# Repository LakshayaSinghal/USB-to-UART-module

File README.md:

# USB-to-UART-module
Small sized PCB for a USB to UART module using CP2102

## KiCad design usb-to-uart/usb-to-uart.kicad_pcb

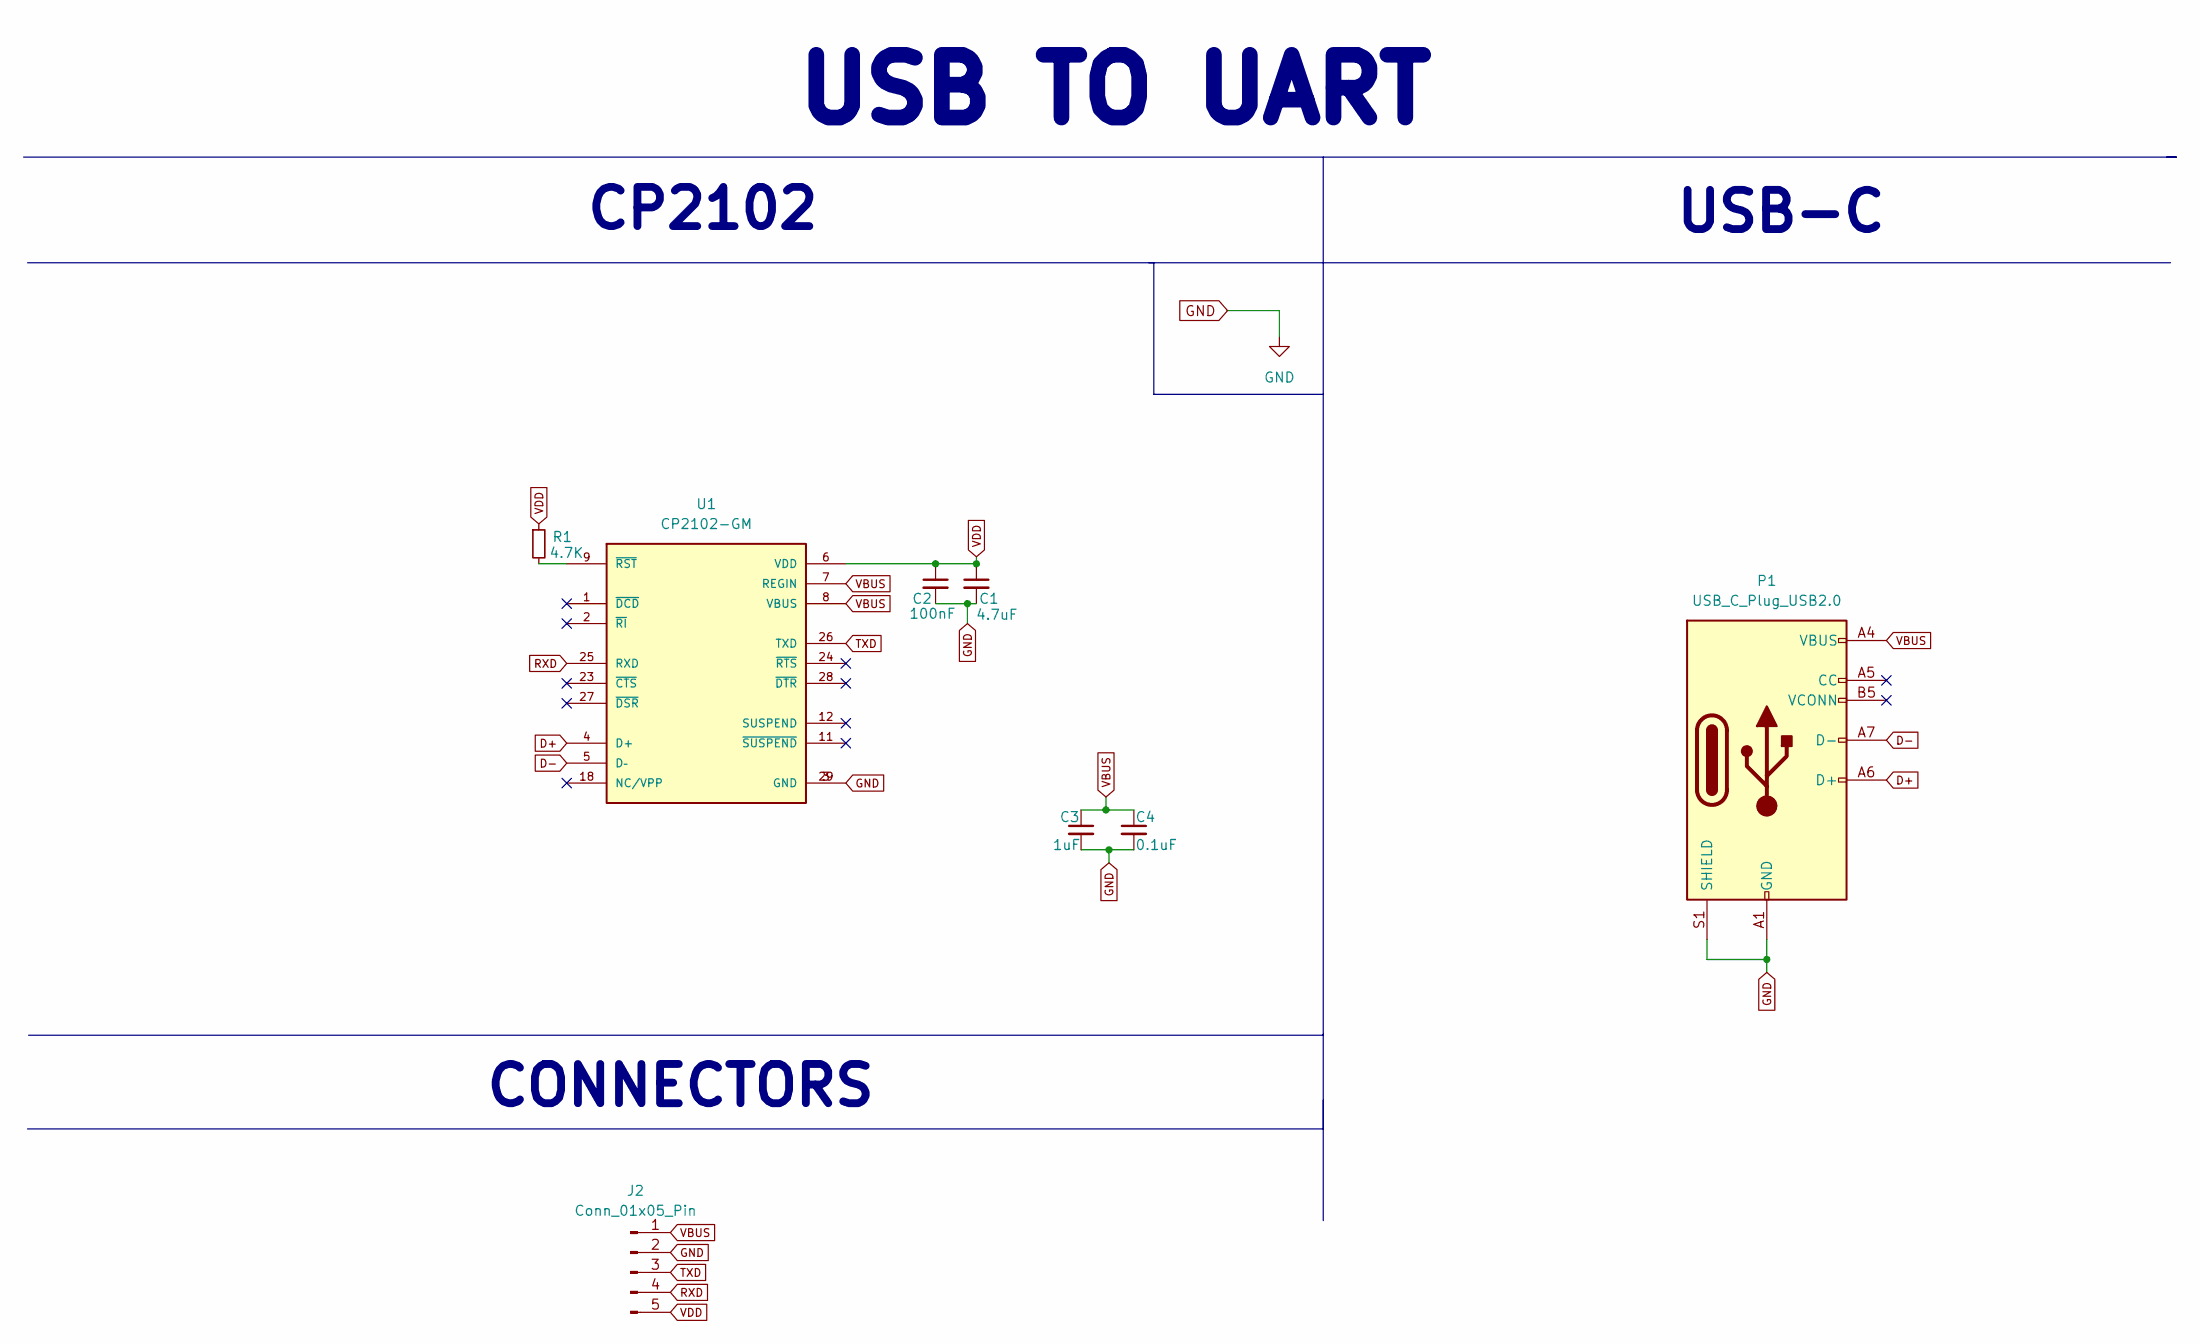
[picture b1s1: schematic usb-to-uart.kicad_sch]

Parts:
C1: 4.7uF; C_0603_1608Metric
C2: 100nF; C_0603_1608Metric
C3: 1uF; C_0603_1608Metric
C4: 0.1uF; C_0603_1608Metric
J2: Conn_01x05_Pin; PinHeader_1x05_P2.54mm_Vertical
P1: USB_C_Plug_USB2.0; USB_C_Receptacle_HRO_TYPE-C-31-M-12
R1: 4.7K; R_0603_1608Metric
U1: CP2102-GM; QFN50P500X500X100-29N; PARTREV 1.8

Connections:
D+: P1.A6 (D+), U1.4 (D+)
D-: P1.A7 (D-), U1.5 (D–)
GND: C1.2, C2.2, C3.2, C4.2, J2.2, P1.A1 (GND), P1.A12 (GND), P1.B1 (GND), P1.B12 (GND), P1.S1 (SHIELD), U1.3 (GND), U1.29 (GND)
unnamed: R1.2, U1.9 (~RST)
RXD: J2.4, U1.25 (RXD)
TXD: J2.3, U1.26 (TXD)
VBUS: C3.1, C4.1, J2.1, P1.A4 (VBUS), P1.A9 (VBUS), P1.B4 (VBUS), P1.B9 (VBUS), U1.7 (REGIN), U1.8 (VBUS)
VDD: C1.1, C2.1, J2.5, R1.1, U1.6 (VDD)

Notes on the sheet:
CP2102
CONNECTORS
USB TO UART
USB-C

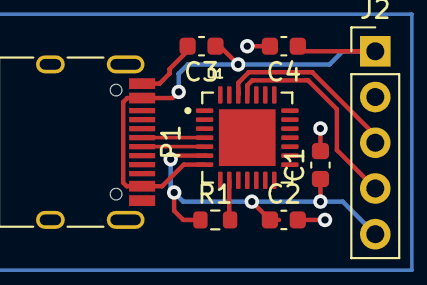
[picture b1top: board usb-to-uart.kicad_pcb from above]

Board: 2 copper layers, 8 parts (0 on the bottom side), 8 nets.

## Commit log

2023-09-03 Added all files for USB to UART pcb
2023-09-03 fixed readme image
